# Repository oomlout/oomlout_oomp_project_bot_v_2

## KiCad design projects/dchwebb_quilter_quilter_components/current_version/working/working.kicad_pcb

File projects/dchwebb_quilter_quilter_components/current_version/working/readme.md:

# quilter
 
## summary 
* id: dchwebb_quilter_quilter_components
* user: dchwebb
* name: quilter
* board: quilter_components
* repo: https://github.com/dchwebb/Quilter
* src_file_repo_kicad_pcb: Quilter_Components.kicad_pcb
* src_file_repo_kicad_pcb_link: https://github.com/dchwebb/Quilter/tree/main/Quilter_Components.kicad_pcb
* src_file_repo_kicad_sch: Filter_Voice.kicad_sch
* src_file_repo_kicad_sch_link: https://github.com/dchwebb/Quilter/tree/main/Filter_Voice.kicad_sch

* src_file_repo_sch: 
* src_file_repo_sch_link: https://github.com/dchwebb/Quilter/tree/main/
* full details link: https://github.com/oomlout/oomlout_oomp_project_bot_v_2/tree/main/projects/dchwebb_quilter_quilter_components/current_version/working

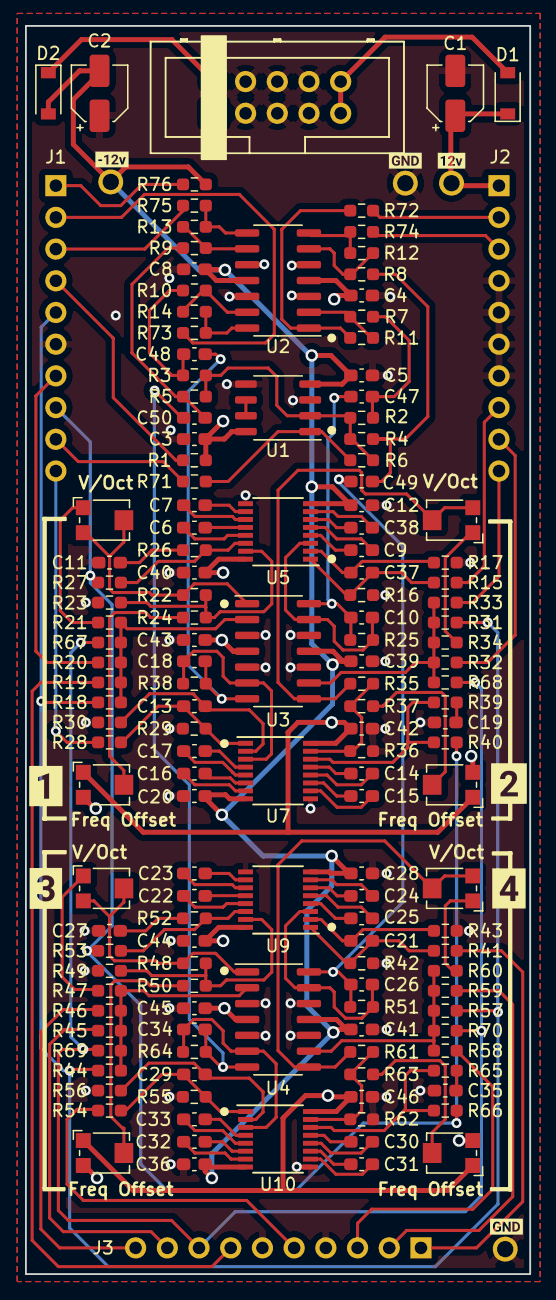
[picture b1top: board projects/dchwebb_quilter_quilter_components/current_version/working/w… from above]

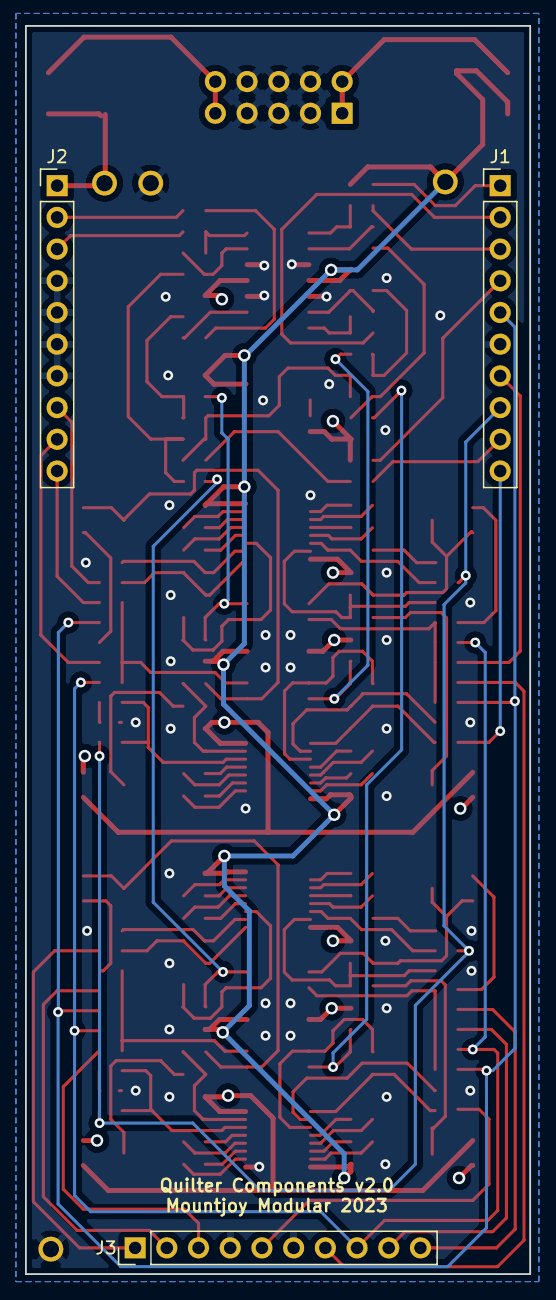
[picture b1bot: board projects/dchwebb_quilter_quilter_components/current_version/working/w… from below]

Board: 4 copper layers, 40.4 x 100.0 mm, 160 parts (3 on the bottom side), 118 nets.

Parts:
C1, C2: 22uF; CP_Elec_4x5.8
C3, C4, C5, C8, C12, C20, C28, C36, C39, C40, C41, C42, C43, C44, C45, C46: 1uF; C_0603_1608Metric_Pad1.08x0.95mm_HandSolder
C6, C7, C14, C15, C16, C22, C23, C24, C30, C31, C32, C38: 6.8nF_C0G; C_0603_1608Metric_Pad1.08x0.95mm_HandSolder
C9, C17, C25, C33: 560pF_C0G; C_0603_1608Metric_Pad1.08x0.95mm_HandSolder
C10, C18, C26, C34: 100pF; C_0603_1608Metric_Pad1.08x0.95mm_HandSolder
C11, C19, C27, C35: 10nF; C_0603_1608Metric_Pad1.08x0.95mm_HandSolder
C13, C21, C29, C37: 3.3nF; C_0603_1608Metric_Pad1.08x0.95mm_HandSolder
C47, C48, C49, C50: 10uF; C_0603_1608Metric_Pad1.08x0.95mm_HandSolder
D1, D2: 1N5819; D_SOD-123
FREQ_OFFSET1, FREQ_OFFSET2, FREQ_OFFSET3, FREQ_OFFSET4: 50k; Potentiometer_Bourns_TC33X_Vertical
J1, J2, J3: Conn_01x10_Male; PinHeader_1x10_P2.54mm_Vertical
J4: Eurorack_10_pin_power; Eurorack_10_pin_header
R1, R76: 14k; R_0603_1608Metric_Pad0.98x0.95mm_HandSolder
R2, R3, R4, R5, R7, R8, R9, R10, R11, R12, R13, R14: 10k; R_0603_1608Metric_Pad0.98x0.95mm_HandSolder
R6: 4.7k; R_0603_1608Metric_Pad0.98x0.95mm_HandSolder
R15, R28, R41, R54: 68k; R_0603_1608Metric_Pad0.98x0.95mm_HandSolder
R16, R17, R29, R30, R42, R43, R55, R56: 200; R_0603_1608Metric_Pad0.98x0.95mm_HandSolder
R18, R20, R22, R31, R33, R35, R44, R46, R48, R57, R59, R61, R67, R68, R69, R70: 100k; R_0603_1608Metric_Pad0.98x0.95mm_HandSolder
R19, R32, R45, R58: 220k; R_0603_1608Metric_Pad0.98x0.95mm_HandSolder
R21, R34, R47, R60: 160k; R_0603_1608Metric_Pad0.98x0.95mm_HandSolder
R23, R36, R49, R62, R71, R72, R73, R74, R75: 1k; R_0603_1608Metric_Pad0.98x0.95mm_HandSolder
R24, R37, R50, R63: 499k; R_0603_1608Metric_Pad0.98x0.95mm_HandSolder
R25, R38, R51, R64: 33k; R_0603_1608Metric_Pad0.98x0.95mm_HandSolder
R26, R39, R52, R65: 499; R_0603_1608Metric_Pad0.98x0.95mm_HandSolder
R27, R40, R53, R66: 24k; R_0603_1608Metric_Pad0.98x0.95mm_HandSolder
TP1, TP2, TP3, TP4: TestPoint; 1.3mm_Test_Point
U1: TL072; SO-8_3.9x4.9mm_P1.27mm
U2, U3, U4: TL074; SOIC-14_3.9x8.7mm_P1.27mm
U5, U7, U9, U10: SSI2144; SSOP-16_3.9x4.9mm_P0.635mm
V_OCT1, V_OCT2, V_OCT3, V_OCT4: 50k; Potentiometer_Bourns_TC33X_Vertical
kibuzzard-63F9EC4B: G***; kibuzzard-63F9EC4B
kibuzzard-63F9ECEE: G***; kibuzzard-63F9ECEE
kibuzzard-63FCE890: G***; kibuzzard-63FCE890
kibuzzard-63FCEF0D: G***; kibuzzard-63FCEF0D
kibuzzard-640237A8: G***; kibuzzard-640237A8
kibuzzard-640237DF, kibuzzard-640237DF#2: G***; kibuzzard-640237DF
kibuzzard-640237FD: G***; kibuzzard-640237FD

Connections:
+12V: C1.1, C3.1, C4.1, C40.1, C42.1, C43.1, C44.1, C45.1, C46.1, D1.1 (K), FREQ_OFFSET1.1, FREQ_OFFSET2.1, FREQ_OFFSET3.1, FREQ_OFFSET4.1, J2.1, R1.1, TP1.1, U1.8 (V+), U2.4 (V+), U3.4 (V+), U4.4 (V+), U5.16 (V+), U7.16 (V+), U9.16 (V+), U10.16 (V+)
-12V: C2.2, C5.1, C8.1, C12.2, C20.2, C28.2, C36.2, C39.1, C41.1, D2.2 (A), FREQ_OFFSET1.3, FREQ_OFFSET2.3, FREQ_OFFSET3.3, FREQ_OFFSET4.3, R76.1, TP2.1, U1.4 (V-), U2.11 (V-), U3.11 (V-), U4.11 (V-), U5.8 (V-), U7.8 (V-), U9.8 (V-), U10.8 (V-)
/+12V_IN: D1.2 (A), J4.9, J4.10
/-12V_IN: D2.1 (K), J4.1, J4.2
/AUDIO_BUFF1: J2.2, R72.2
/AUDIO_BUFF2: J1.2, R73.2
/AUDIO_BUFF3: J2.3, R74.2
/AUDIO_BUFF4: J1.3, R75.2
/AUDIO_IN1: J2.8, R15.2
/AUDIO_IN2: J1.10, R28.2
/AUDIO_IN3: J3.1, R41.2
/AUDIO_IN4: J3.5, R54.2
/AUDIO_MIX: J1.9, R71.2
/Audio_Out1: C47.1, R2.2, R7.2
/Audio_Out2: C48.1, R3.2, R10.2
/Audio_Out3: C49.1, R4.2, R8.2
/Audio_Out4: C50.1, R5.2, R9.2
/FREQ_CV_DAMP1: J3.7, R19.2
/FREQ_CV_DAMP2: J2.9, R32.2
/FREQ_CV_DAMP3: J3.9, R45.2
/FREQ_CV_DAMP4: J3.3, R58.2
/FREQ_JACK: J3.8, R67.2, R68.2, R69.2, R70.2
/FREQ_POT: J1.5, R18.2, R31.2, R44.2, R57.2
/FREQ_POT_5V: J1.4, R1.2
/FREQ_POT_-5V: J1.1, R76.2
/FREQ_V_OCT1: J1.7, R20.2
/FREQ_V_OCT2: J2.10, R33.2
/FREQ_V_OCT3: J3.10, R46.2
/FREQ_V_OCT4: J3.2, R59.2
/Filter_Voice1/FREQ_CTRL: R22.1, R23.1, R24.1, U5.15 (FREQ_CTRL)
/Filter_Voice1/Q_CTRL: R26.2, R27.2, U5.14 (Q_CTRL)
/Filter_Voice2/FREQ_CTRL: R35.1, R36.1, R37.1, U7.15 (FREQ_CTRL)
/Filter_Voice2/Q_CTRL: R39.2, R40.2, U7.14 (Q_CTRL)
/Filter_Voice3/FREQ_CTRL: R48.1, R49.1, R50.1, U9.15 (FREQ_CTRL)
/Filter_Voice3/Q_CTRL: R52.2, R53.2, U9.14 (Q_CTRL)
/Filter_Voice4/FREQ_CTRL: R61.1, R62.1, R63.1, U10.15 (FREQ_CTRL)
/Filter_Voice4/Q_CTRL: R65.2, R66.2, U10.14 (Q_CTRL)
/Q_POT: J1.8, R27.1, R40.1, R53.1, R66.1
GND: C1.2, C2.1, C3.2, C4.2, C5.2, C8.2, C11.2, C12.1, C19.2, C20.1, C27.2, C28.1, C35.2, C36.1, C39.2, C40.2, C41.2, C42.2, C43.2, C44.2, C45.2, C46.2, J1.6, J2.4, J2.5, J2.6, J2.7, J3.4, J3.6, J4.3, J4.4, J4.5, J4.6, J4.7, J4.8, R16.1, R17.2, R23.2, R29.1, R30.2, R36.2, R42.1, R43.2, R49.2, R55.1, R56.2, R62.2, TP3.1, TP4.1, U1.3 (+), U1.5 (+), U2.3 (+), U2.5 (+), U2.10 (+), U2.12 (+), U3.3 (+), U3.5 (+), U3.10 (+), U3.12 (+), U4.3 (+), U4.5 (+), U4.10 (+), U4.12 (+), U5.9 (GND), U7.9 (GND), U9.9 (GND), U10.9 (GND)
unnamed: C6.1, U5.13 (C1A)
unnamed: C6.2, U5.12 (C1B)
unnamed: C7.1, U5.11 (C2A)
unnamed: C7.2, U5.10 (C2B)
unnamed: C9.1, U5.4 (C4A)
unnamed: C9.2, U5.5 (C4B)
unnamed: C10.1, C47.2, R25.1, U3.14
unnamed: C10.2, R25.2, U3.13 (-), U5.3 (OUT)
unnamed: C11.1, R26.1
unnamed: C13.1, R30.1, U7.2 (SIG_IN-)
unnamed: C13.2, R28.1, R29.2, U7.1 (SIG_IN+)
unnamed: C14.1, U7.13 (C1A)
unnamed: C14.2, U7.12 (C1B)
unnamed: C15.1, U7.11 (C2A)
unnamed: C15.2, U7.10 (C2B)
unnamed: C16.1, U7.6 (C3A)
unnamed: C16.2, U7.7 (C3B)
unnamed: C17.1, U7.4 (C4A)
unnamed: C17.2, U7.5 (C4B)
unnamed: C18.1, C48.2, R38.1, U3.7
unnamed: C18.2, R38.2, U3.6 (-), U7.3 (OUT)
unnamed: C19.1, R39.1
unnamed: C21.1, R43.1, U9.2 (SIG_IN-)
unnamed: C21.2, R41.1, R42.2, U9.1 (SIG_IN+)
unnamed: C22.1, U9.13 (C1A)
unnamed: C22.2, U9.12 (C1B)
unnamed: C23.1, U9.11 (C2A)
unnamed: C23.2, U9.10 (C2B)
unnamed: C24.1, U9.6 (C3A)
unnamed: C24.2, U9.7 (C3B)
unnamed: C25.1, U9.4 (C4A)
unnamed: C25.2, U9.5 (C4B)
unnamed: C26.1, C49.2, R51.1, U4.14
unnamed: C26.2, R51.2, U4.13 (-), U9.3 (OUT)
unnamed: C27.1, R52.1
unnamed: C29.1, R56.1, U10.2 (SIG_IN-)
unnamed: C29.2, R54.1, R55.2, U10.1 (SIG_IN+)
unnamed: C30.1, U10.13 (C1A)
unnamed: C30.2, U10.12 (C1B)
unnamed: C31.1, U10.11 (C2A)
unnamed: C31.2, U10.10 (C2B)
unnamed: C32.1, U10.6 (C3A)
unnamed: C32.2, U10.7 (C3B)
unnamed: C33.1, U10.4 (C4A)
unnamed: C33.2, U10.5 (C4B)
unnamed: C34.1, C50.2, R64.1, U4.7
unnamed: C34.2, R64.2, U4.6 (-), U10.3 (OUT)
unnamed: C35.1, R65.1
unnamed: C37.1, R17.1, U5.2 (SIG_IN-)
unnamed: C37.2, R15.1, R16.2, U5.1 (SIG_IN+)
unnamed: C38.1, U5.6 (C3A)
unnamed: C38.2, U5.7 (C3B)
unnamed: FREQ_OFFSET1.2, R24.2
unnamed: FREQ_OFFSET2.2, R37.2
unnamed: FREQ_OFFSET3.2, R50.2
unnamed: FREQ_OFFSET4.2, R63.2
unnamed: R2.1, R3.1, R4.1, R5.1, R6.2, U1.2 (-)
unnamed: R6.1, R71.1, U1.1
unnamed: R10.1, R14.2, U2.13 (-)
unnamed: R11.1, R72.1, U2.1
unnamed: R7.1, R11.2, U2.2 (-)
unnamed: R12.1, R74.1, U2.7
unnamed: R8.1, R12.2, U2.6 (-)
unnamed: R13.1, R75.1, U2.8
unnamed: R9.1, R13.2, U2.9 (-)
unnamed: R14.1, R73.1, U2.14
unnamed: R18.1, R19.1, R20.1, R21.2, R67.1, U3.2 (-)
unnamed: R21.1, V_OCT1.1
unnamed: R22.2, U3.1, V_OCT1.2, V_OCT1.3
unnamed: R31.1, R32.1, R33.1, R34.2, R68.1, U3.9 (-)
unnamed: R34.1, V_OCT2.1
unnamed: R35.2, U3.8, V_OCT2.2, V_OCT2.3
unnamed: R44.1, R45.1, R46.1, R47.2, R69.1, U4.2 (-)
unnamed: R47.1, V_OCT3.1
unnamed: R48.2, U4.1, V_OCT3.2, V_OCT3.3
unnamed: R57.1, R58.1, R59.1, R60.2, R70.1, U4.9 (-)
unnamed: R60.1, V_OCT4.1
unnamed: R61.2, U4.8, V_OCT4.2, V_OCT4.3
unnamed: U1.6 (-), U1.7

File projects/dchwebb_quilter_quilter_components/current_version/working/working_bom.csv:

"Id";"Designator";"Footprint";"Quantity";"Designation";"Supplier and ref";
1;"R44,R35,R57,R33,R46,R22,R18,R69,R68,R67,R20,R70,R48,R59,R31,R61";"R_0603_1608Metric_Pad0.98x0.95mm_HandSolder";16;"100k";;;
2;"R23,R75,R73,R74,R62,R36,R72,R71,R49";"R_0603_1608Metric_Pad0.98x0.95mm_HandSolder";9;"1k";;;
3;"C4,C45,C3,C28,C40,C5,C46,C36,C12,C44,C8,C41,C43,C42,C39,C20";"C_0603_1608Metric_Pad1.08x0.95mm_HandSolder";16;"1uF";;;
4;"D1,D2";"D_SOD-123";2;"1N5819";;;
5;"R53,R27,R40,R66";"R_0603_1608Metric_Pad0.98x0.95mm_HandSolder";4;"24k";;;
6;"C38,C14,C30,C15,C31,C22,C24,C16,C6,C23,C32,C7";"C_0603_1608Metric_Pad1.08x0.95mm_HandSolder";12;"6.8nF_C0G";;;
7;"R58,R19,R32,R45";"R_0603_1608Metric_Pad0.98x0.95mm_HandSolder";4;"220k";;;
8;"C10,C18,C34,C26";"C_0603_1608Metric_Pad1.08x0.95mm_HandSolder";4;"100pF";;;
9;"R2,R9,R13,R10,R3,R7,R12,R8,R4,R14,R5,R11";"R_0603_1608Metric_Pad0.98x0.95mm_HandSolder";12;"10k";;;
10;"R21,R34,R47,R60";"R_0603_1608Metric_Pad0.98x0.95mm_HandSolder";4;"160k";;;
11;"R42,R16,R56,R55,R30,R17,R43,R29";"R_0603_1608Metric_Pad0.98x0.95mm_HandSolder";8;"200";;;
12;"C11,C19,C27,C35";"C_0603_1608Metric_Pad1.08x0.95mm_HandSolder";4;"10nF";;;
13;"R51,R38,R64,R25";"R_0603_1608Metric_Pad0.98x0.95mm_HandSolder";4;"33k";;;
14;"C21,C37,C13,C29";"C_0603_1608Metric_Pad1.08x0.95mm_HandSolder";4;"3.3nF";;;
15;"R6";"R_0603_1608Metric_Pad0.98x0.95mm_HandSolder";1;"4.7k";;;
16;"R54,R28,R41,R15";"R_0603_1608Metric_Pad0.98x0.95mm_HandSolder";4;"68k";;;
17;"C49,C47,C50,C48";"C_0603_1608Metric_Pad1.08x0.95mm_HandSolder";4;"10uF";;;
18;"U1";"SO-8_3.9x4.9mm_P1.27mm";1;"TL072";;;

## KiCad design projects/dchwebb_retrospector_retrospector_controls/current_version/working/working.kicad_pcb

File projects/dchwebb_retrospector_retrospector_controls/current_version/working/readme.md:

# retrospector
 
## summary 
* id: dchwebb_retrospector_retrospector_controls
* user: dchwebb
* name: retrospector
* board: retrospector_controls
* repo: https://github.com/dchwebb/Retrospector
* src_file_repo_kicad_pcb: Hardware/Retrospector_Components.kicad_pcb
* src_file_repo_kicad_pcb_link: https://github.com/dchwebb/Retrospector/tree/master/Hardware/Retrospector_Components.kicad_pcb
* src_file_repo_kicad_sch: Hardware/Retrospector_Components.kicad_sch
* src_file_repo_kicad_sch_link: https://github.com/dchwebb/Retrospector/tree/master/Hardware/Retrospector_Components.kicad_sch

* src_file_repo_sch: Hardware/Retrospector_Components.sch
* src_file_repo_sch_link: https://github.com/dchwebb/Retrospector/tree/master/Hardware/Retrospector_Components.sch
* full details link: https://github.com/oomlout/oomlout_oomp_project_bot_v_2/tree/main/projects/dchwebb_retrospector_retrospector_controls/current_version/working

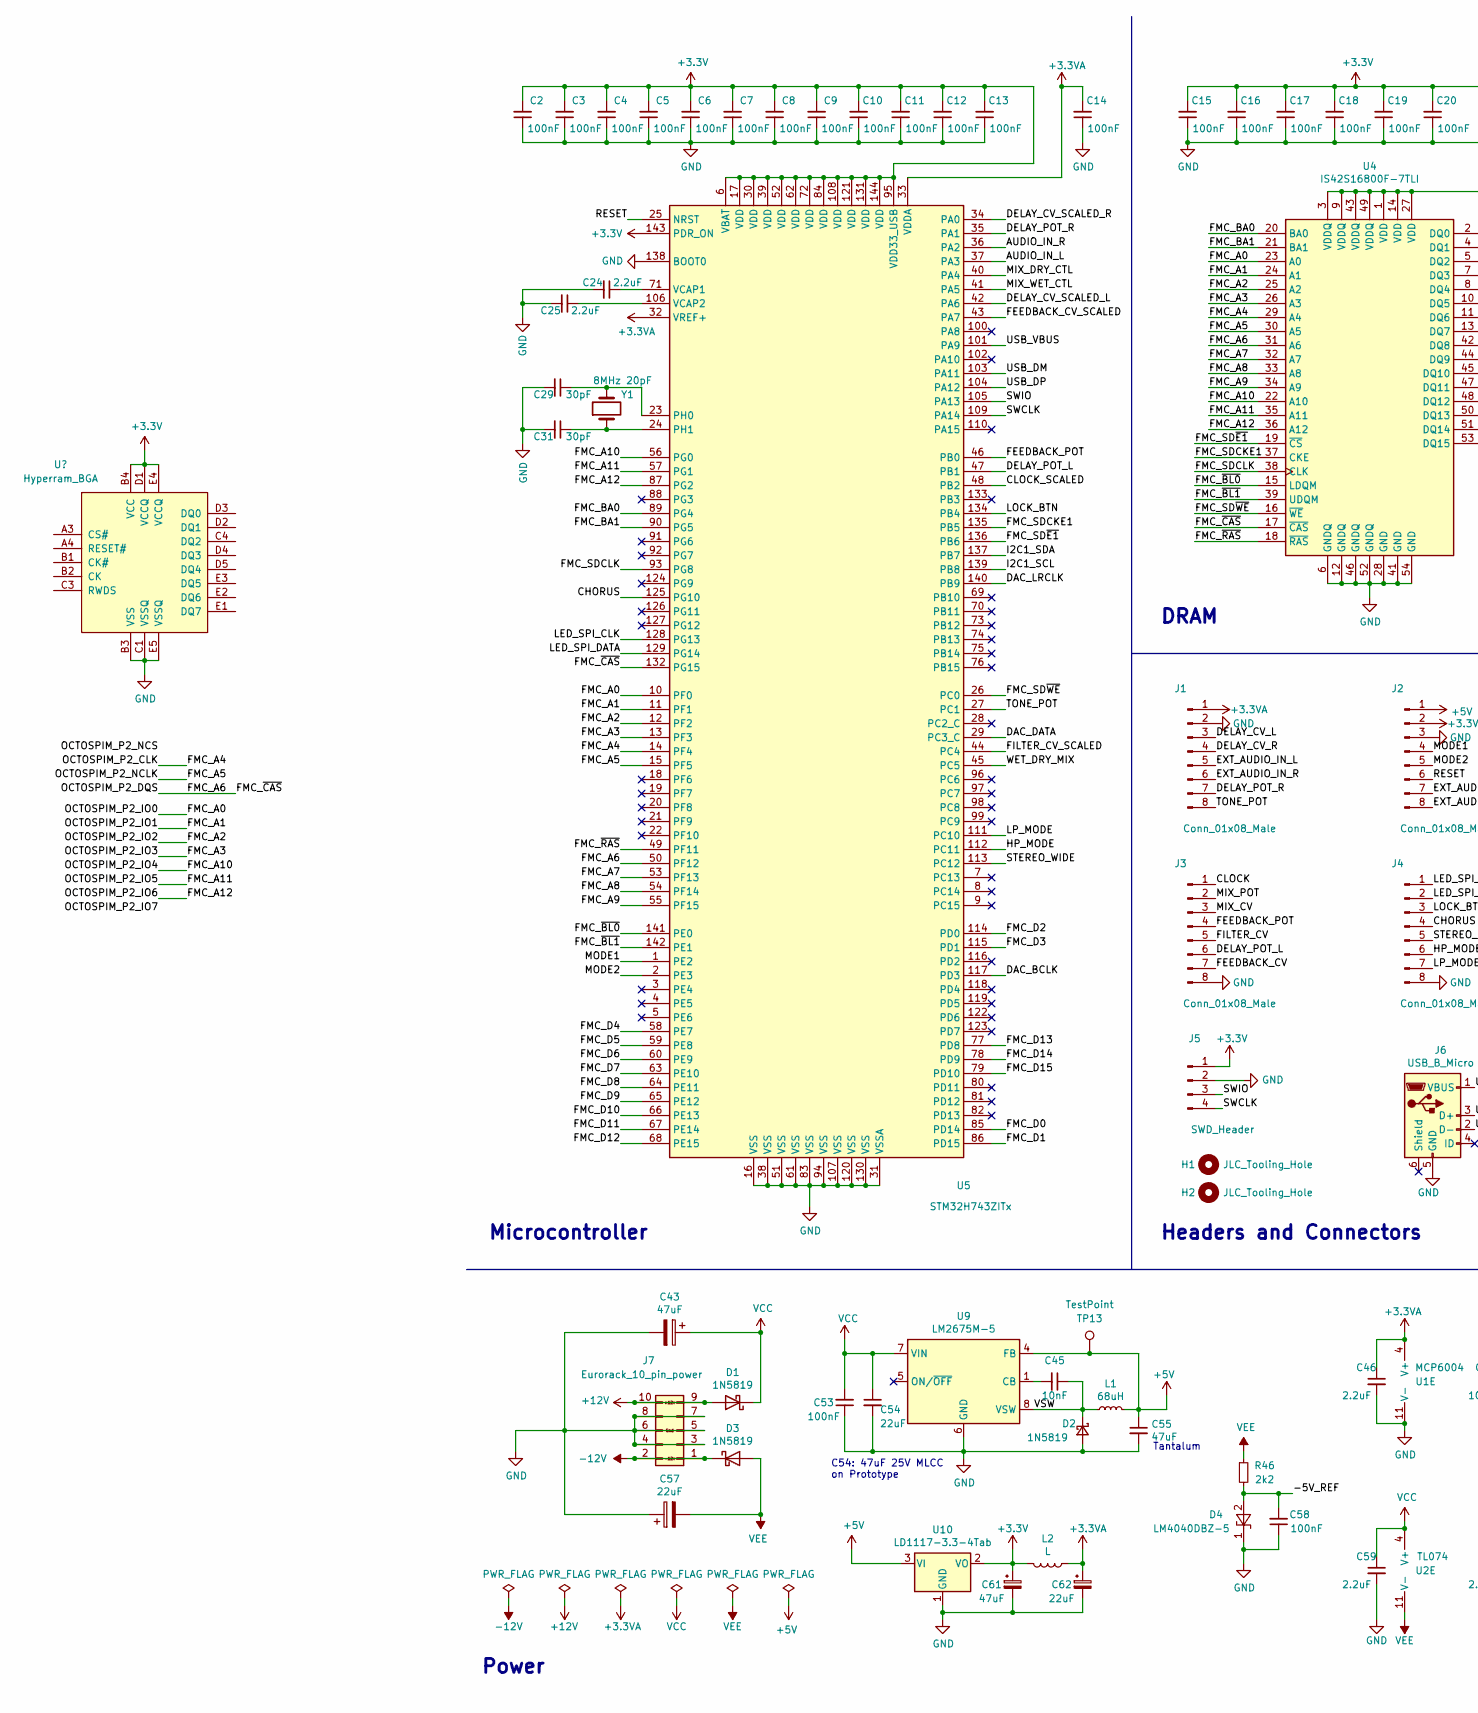
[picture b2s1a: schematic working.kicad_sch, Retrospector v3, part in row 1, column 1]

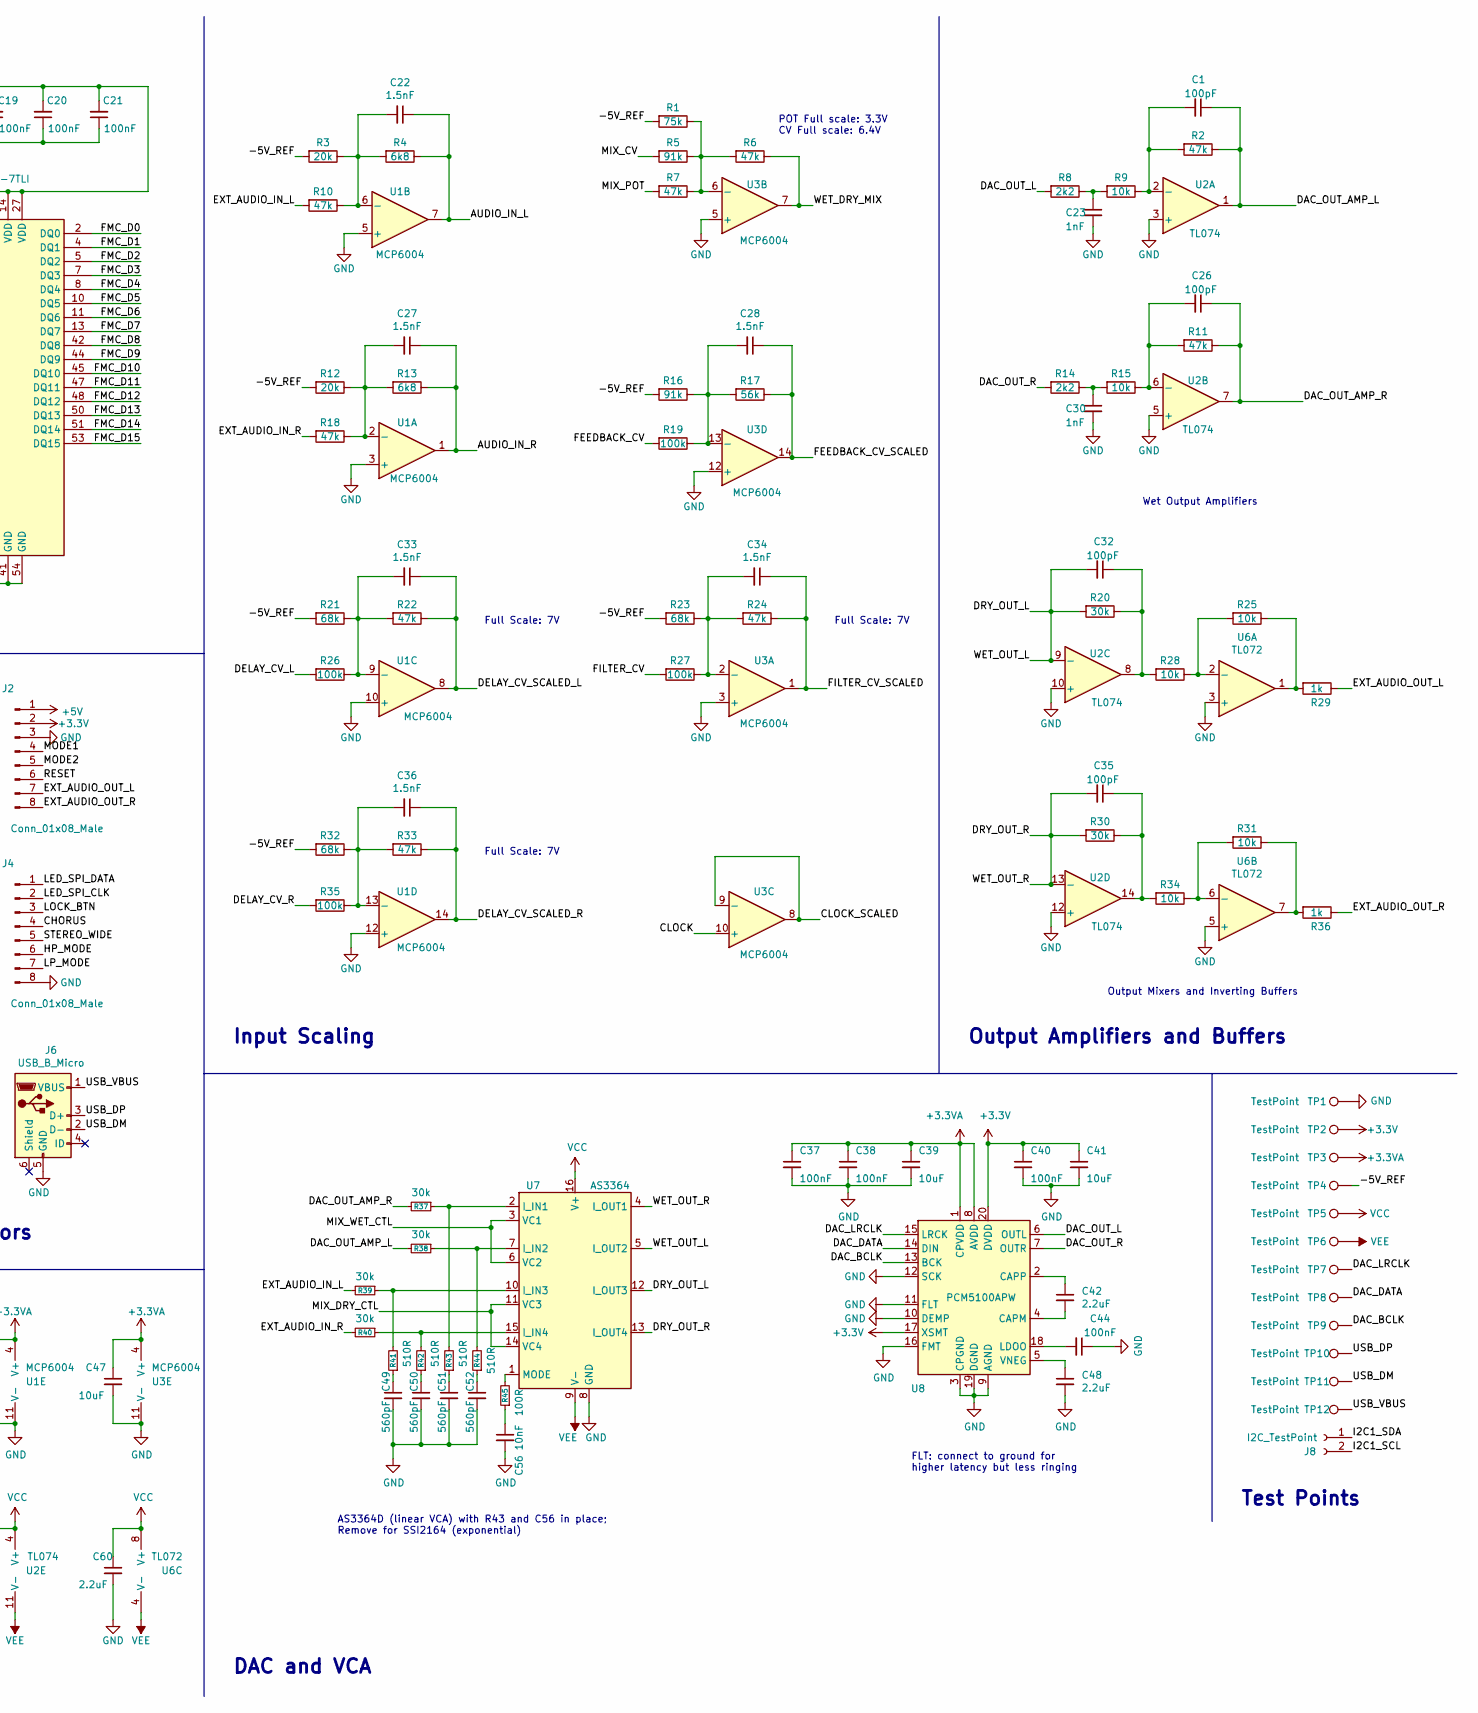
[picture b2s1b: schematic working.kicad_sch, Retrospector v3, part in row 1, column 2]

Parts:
C1, C26, C32, C35: 100pF; C_0603_HandSoldering; Part_Number C14858
C2, C3, C4, C5, C6, C7, C8, C9, C10, C11, C12, C13, C14, C15, C16, C17, C18, C19, C20, C21, C37, C38, C40, C44, C58: 100nF; C_0603_HandSoldering; Part_Number C14663
C22, C27, C28, C33, C34, C36: 1.5nF; C_0603_HandSoldering; Part_Number C1595
C23, C30: 1nF; C_0603_HandSoldering; Part_Number C1588
C24, C25, C42, C46, C48, C59, C60: 2.2uF; C_0603_HandSoldering; Part_Number C23630
C29, C31: 30pF; C_0603_HandSoldering; Part_Number C22397
C39, C41, C47: 10uF; C_0805; Part_Number C15850
C43, C61: 47uF; CP_Elec_5x5.8; Part_Number C134798
C45, C56: 10nF; C_0603_HandSoldering; Part_Number C57112
C49, C50, C51, C52: 560pF; C_0603_HandSoldering; Part_Number C84721
C53: 100nF; C_0603_HandSoldering
C54: 22uF; C_1210
C55: 47uF; C_1210
C57, C62: 22uF; CP_Elec_4x5.8; Part_Number C134793
D1, D2, D3: 1N5819; D_SOD-123; Part_Number C8598
D4: LM4040DBZ-5; SOT-23; Part_Number C156291
H1, H2: JLC_Tooling_Hole; JLC_SMT_Tooling_Hole
J1, J2, J3, J4: Conn_01x08_Male; Pin_Header_Straight_1x08_Pitch2.54mm
J5: SWD_Header; SWD_header
J6: USB_B_Micro; USB_Micro-B_Amphenol
J7: Eurorack_10_pin_power; Eurorack_10_pin_header
J8: I2C_TestPoint; Pin_Header_Straight_1x02_Pitch2.54mm
L1: 68uH; TDK_Inductor_6.9x7.2
L2: L; L_0805_HandSoldering; Part_Number C1046
R1: 75k; R_0603_HandSoldering; Part_Number C23242
R2, R6, R7, R10, R11, R18, R22, R24, R33: 47k; R_0603_HandSoldering; Part_Number C25819
R3, R12: 20k; R_0603_HandSoldering; Part_Number C4184
R4, R13: 6k8; R_0603_HandSoldering; Part_Number C23212
R5, R16: 91k; R_0603_HandSoldering; Part_Number C23265
R8, R14, R46: 2k2; R_0603_HandSoldering; Part_Number C4190
R9, R15, R25, R28, R31, R34: 10k; R_0603_HandSoldering; Part_Number C25804
R17: 56k; R_0603_HandSoldering; Part_Number C23206
R19, R26, R27, R35: 100k; R_0603_HandSoldering; Part_Number C25803
R20, R30, R37, R38, R39, R40: 30k; R_0603_HandSoldering; Part_Number C22984
R21, R23, R32: 68k; R_0603_HandSoldering; Part_Number C23231
R29, R36: 1k; R_0603_HandSoldering; Part_Number C21190
R41, R42, R43, R44: 510R; R_0603_HandSoldering; Part_Number C23193
R45: 100R; R_0603_HandSoldering; Part_Number C22775
TP1, TP2, TP3, TP4, TP5, TP6: TestPoint; 1.3mm_Test_Point
TP7, TP8, TP9, TP10, TP11, TP12, TP13: TestPoint; Measurement_Point_Square-SMD-Pad_Small
U1, U3: MCP6004; SOIC-14_N; Part_Number C116668
U2: TL074; SOIC-14_N; Part_Number C6964
U4: IS42S16800F-7TLI; TSOP-II-54_22.2x10.16mm_P0.8mm; Part_Number C91278
U5: STM32H743ZITx; LQFP-144_20x20mm_P0.5mm; Part_Number C114408
U6: TL072; SOIC-8_3.9x4.9mm_Pitch1.27mm; Part_Number C6961
U7: AS3364; SOIC-16_3.9x9.9mm_Pitch1.27mm
U8: PCM5100APW; SSOP-20_4.4x6.5mm_Pitch0.65mm_Round_Pads; Part_Number C131154
U9: LM2675M-5; SOIC-8_3.9x4.9mm_Pitch1.27mm; Part_Number C180371
U10: LD1117-3.3-4Tab; SOT-223-3_TabPin2
Y1: 8MHz 20pF; Crystal_SMD_5032-2pin_5.0x3.2mm_HandSoldering; Part_Number C115962

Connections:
+3.3VA: C14.2, C37.1, C38.1, C39.1, C46.1, C47.1, C62.1, J1.1, L2.1, TP3.1, U1.4 (V+), U3.4 (V+), U5.32 (VREF+), U5.33 (VDDA), U8.1 (CPVDD), U8.8 (AVDD)
+3V3: C2.2, C3.2, C4.2, C5.2, C6.2, C7.2, C8.2, C9.2, C10.2, C11.2, C12.2, C13.2, C15.2, C16.2, C17.2, C18.2, C19.2, C20.2, C21.2, C40.1, C41.1, C61.1, J2.2, J5.1, L2.2, TP2.1, U4.1 (VDD), U4.3 (VDDQ), U4.9 (VDDQ), U4.14 (VDD), U4.27 (VDD), U4.43 (VDDQ), U4.49 (VDDQ), U5.6 (VBAT), U5.17 (VDD), U5.30 (VDD), U5.39 (VDD), U5.52 (VDD), U5.62 (VDD), U5.72 (VDD), U5.84 (VDD), U5.95 (VDD33_USB), U5.108 (VDD), U5.121 (VDD), U5.131 (VDD), U5.143 (PDR_ON), U5.144 (VDD), U8.17 (XSMT), U8.20 (DVDD), U10.2 (VO)
+5V: C55.1, J2.1, L1.2, TP13.1, U9.4 (FB), U10.3 (VI)
+12V: D1.2 (A), J7.9, J7.10
-12V: D3.1 (K), J7.1, J7.2
/-5V_REF: C58.2, D4.2 (A), R1.2, R3.2, R12.2, R16.2, R21.2, R23.2, R32.2, R46.2, TP4.1
/AUDIO_IN_L: C22.1, R4.1, U1.7, U5.37 (PA3)
/AUDIO_IN_R: C27.1, R13.1, U1.1, U5.36 (PA2)
/CHORUS: J4.4, U5.125 (PG10)
/CLOCK: J3.1, U3.10 (+)
/CLOCK_SCALED: U3.8, U3.9 (-), U5.48 (PB2)
/DAC_BCLK: TP9.1, U5.117 (PD3), U8.13 (BCK)
/DAC_DATA: TP8.1, U5.29 (PC3_C), U8.14 (DIN)
/DAC_LRCLK: TP7.1, U5.140 (PB9), U8.15 (LRCK)
/DAC_OUT_AMP_L: C1.1, R2.1, R38.2, U2.1
/DAC_OUT_AMP_R: C26.1, R11.1, R37.2, U2.7
/DAC_OUT_L: R8.2, U8.6 (OUTL)
/DAC_OUT_R: R14.2, U8.7 (OUTR)
/DELAY_CV_L: J1.3, R26.2
/DELAY_CV_R: J1.4, R35.2
/DELAY_CV_SCALED_L: C33.1, R22.1, U1.8, U5.42 (PA6)
/DELAY_CV_SCALED_R: C36.1, R33.1, U1.14, U5.34 (PA0)
/DELAY_POT_L: J3.6, U5.47 (PB1)
/DELAY_POT_R: J1.7, U5.35 (PA1)
/DRY_OUT_L: C32.2, R20.2, U2.9 (-), U7.5 (I_OUT2), U7.12 (I_OUT3)
/DRY_OUT_R: C35.2, R30.2, U2.13 (-), U7.4 (I_OUT1), U7.13 (I_OUT4)
/EXT_AUDIO_IN_L: J1.5, R10.2, R39.2
/EXT_AUDIO_IN_R: J1.6, R18.2, R40.2
/EXT_AUDIO_OUT_L: J2.7, R29.1
/EXT_AUDIO_OUT_R: J2.8, R36.1
/FEEDBACK_CV: J3.7, R19.2
/FEEDBACK_CV_SCALED: C28.1, R17.1, U3.14, U5.43 (PA7)
/FEEDBACK_POT: J3.4, U5.46 (PB0)
/FILTER_CV: J3.5, R27.2
/FILTER_CV_SCALED: C34.1, R24.1, U3.1, U5.44 (PC4)
/FMC_A0: U4.23 (A0), U5.10 (PF0)
/FMC_A1: U4.24 (A1), U5.11 (PF1)
/FMC_A2: U4.25 (A2), U5.12 (PF2)
/FMC_A3: U4.26 (A3), U5.13 (PF3)
/FMC_A4: U4.29 (A4), U5.14 (PF4)
/FMC_A5: U4.30 (A5), U5.15 (PF5)
/FMC_A7: U4.32 (A7), U5.53 (PF13)
/FMC_A8: U4.33 (A8), U5.54 (PF14)
/FMC_A9: U4.34 (A9), U5.55 (PF15)
/FMC_A10: U4.22 (A10), U5.56 (PG0)
/FMC_A11: U4.35 (A11), U5.57 (PG1)
/FMC_A12: U4.36 (A12), U5.87 (PG2)
/FMC_BA0: U4.20 (BA0), U5.89 (PG4)
/FMC_BA1: U4.21 (BA1), U5.90 (PG5)
/FMC_D0: U4.2 (DQ0), U5.85 (PD14)
/FMC_D1: U4.4 (DQ1), U5.86 (PD15)
/FMC_D2: U4.5 (DQ2), U5.114 (PD0)
/FMC_D3: U4.7 (DQ3), U5.115 (PD1)
/FMC_D4: U4.8 (DQ4), U5.58 (PE7)
/FMC_D5: U4.10 (DQ5), U5.59 (PE8)
/FMC_D6: U4.11 (DQ6), U5.60 (PE9)
/FMC_D7: U4.13 (DQ7), U5.63 (PE10)
/FMC_D8: U4.42 (DQ8), U5.64 (PE11)
/FMC_D9: U4.44 (DQ9), U5.65 (PE12)
/FMC_D10: U4.45 (DQ10), U5.66 (PE13)
/FMC_D11: U4.47 (DQ11), U5.67 (PE14)
/FMC_D12: U4.48 (DQ12), U5.68 (PE15)
/FMC_D13: U4.50 (DQ13), U5.77 (PD8)
/FMC_D14: U4.51 (DQ14), U5.78 (PD9)
/FMC_D15: U4.53 (DQ15), U5.79 (PD10)
/FMC_SDCKE1: U4.37 (CKE), U5.135 (PB5)
/FMC_SDCLK: U4.38 (CLK), U5.93 (PG8)
/FMC_SD~E1: U4.19 (~CS), U5.136 (PB6)
/FMC_SD~WE: U4.16 (~WE), U5.26 (PC0)
/FMC_~BL0: U4.15 (LDQM), U5.141 (PE0)
/FMC_~BL1: U4.39 (UDQM), U5.142 (PE1)
/FMC_~RAS: U4.18 (~RAS), U5.49 (PF11)
/HP_MODE: J4.6, U5.112 (PC11)
/I2C1_SCL: J8.2, U5.139 (PB8)
/I2C1_SDA: J8.1, U5.137 (PB7)
/LED_SPI_CLK: J4.2, U5.128 (PG13)
/LED_SPI_DATA: J4.1, U5.129 (PG14)
/LOCK_BTN: J4.3, U5.134 (PB4)
/LP_MODE: J4.7, U5.111 (PC10)
/MIX_CV: J3.3, R5.2
/MIX_DRY_CTL: U5.40 (PA4), U7.11 (VC3), U7.14 (VC4)
/MIX_POT: J3.2, R7.2
/MIX_WET_CTL: U5.41 (PA5), U7.3 (VC1), U7.6 (VC2)
/MODE1: J2.4, U5.1 (PE2)
/MODE2: J2.5, U5.2 (PE3)
/RESET: J2.6, U5.25 (NRST)
/STEREO_WIDE: J4.5, U5.113 (PC12)
/SWCLK: J5.4, U5.109 (PA14)
/SWIO: J5.3, U5.105 (PA13)
/TONE_POT: J1.8, U5.27 (PC1)
/USB_DM: J6.2 (D-), TP11.1, U5.103 (PA11)
/USB_DP: J6.3 (D+), TP10.1, U5.104 (PA12)
/USB_VBUS: J6.1 (VBUS), TP12.1, U5.101 (PA9)
/VSW: C45.1, D2.1 (K), L1.1, U9.8 (VSW)
/WET_DRY_MIX: R6.1, U3.7, U5.45 (PC5)
GND: C2.1, C3.1, C4.1, C5.1, C6.1, C7.1, C8.1, C9.1, C10.1, C11.1, C12.1, C13.1, C14.1, C15.1, C16.1, C17.1, C18.1, C19.1, C20.1, C21.1, C23.2, C24.2, C25.2, C29.2, C30.2, C31.2, C37.2, C38.2, C39.2, C40.2, C41.2, C43.2, C44.1, C46.2, C47.2, C48.2, C49.2, C50.2, C51.2, C52.2, C53.1, C54.2, C55.2, C56.2, C57.1, C58.1, C59.2, C60.2, C61.2, C62.2, D2.2 (A), D4.1 (K), J1.2, J2.3, J3.8, J4.8, J5.2, J6.5 (GND), J7.3, J7.4, J7.5, J7.6, J7.7, J7.8, TP1.1, U1.3 (+), U1.5 (+), U1.10 (+), U1.11 (V-), U1.12 (+), U2.3 (+), U2.5 (+), U2.10 (+), U2.12 (+), U3.3 (+), U3.5 (+), U3.11 (V-), U3.12 (+), U4.6 (GNDQ), U4.12 (GNDQ), U4.28 (GND), U4.41 (GND), U4.46 (GNDQ), U4.52 (GNDQ), U4.54 (GND), U5.16 (VSS), U5.31 (VSSA), U5.38 (VSS), U5.51 (VSS), U5.61 (VSS), U5.83 (VSS), U5.94 (VSS), U5.107 (VSS), U5.120 (VSS), U5.130 (VSS), U5.138 (BOOT0), U6.3 (+), U6.5 (+), U7.8 (GND), U8.3 (CPGND), U8.9 (AGND), U8.10 (DEMP), U8.11 (FLT), U8.12 (SCK), U8.16 (FMT), U8.19 (DGND), U9.6 (GND), U10.1 (GND)
unnamed: C1.2, R2.2, R9.1, U2.2 (-)
unnamed: C22.2, R3.1, R4.2, R10.1, U1.6 (-)
unnamed: C23.1, R8.1, R9.2
unnamed: C24.1, U5.71 (VCAP1)
unnamed: C25.1, U5.106 (VCAP2)
unnamed: C26.2, R11.2, R15.1, U2.6 (-)
unnamed: C27.2, R12.1, R13.2, R18.1, U1.2 (-)
unnamed: C28.2, R16.1, R17.2, R19.1, U3.13 (-)
unnamed: C29.1, U5.23 (PH0), Y1.2
unnamed: C30.1, R14.1, R15.2
unnamed: C31.1, U5.24 (PH1), Y1.1
unnamed: C32.1, R20.1, R28.2, U2.8
unnamed: C33.2, R21.1, R22.2, R26.1, U1.9 (-)
unnamed: C34.2, R23.1, R24.2, R27.1, U3.2 (-)
unnamed: C35.1, R30.1, R34.2, U2.14
unnamed: C36.2, R32.1, R33.2, R35.1, U1.13 (-)
unnamed: C42.1, U8.2 (CAPP)
unnamed: C42.2, U8.4 (CAPM)
unnamed: C44.2, U8.18 (LDOO)
unnamed: C45.2, U9.1 (CB)
unnamed: C48.1, U8.5 (VNEG)
unnamed: C49.1, R41.1
unnamed: C50.1, R42.1
unnamed: C51.1, R43.1
unnamed: C52.1, R44.1
unnamed: C56.1, R45.1
unnamed: R1.1, R5.1, R6.2, R7.1, U3.6 (-)
unnamed: R25.1, R29.2, U6.1
unnamed: R25.2, R28.1, U6.2 (-)
unnamed: R31.1, R36.2, U6.7
unnamed: R31.2, R34.1, U6.6 (-)
unnamed: R37.1, R43.2, U7.2 (I_IN1)
unnamed: R38.1, R44.2, U7.7 (I_IN2)
unnamed: R39.1, R41.2, U7.10 (I_IN3)
unnamed: R40.1, R42.2, U7.15 (I_IN4)
unnamed: R45.2, U7.1 (MODE)
VCC: C43.1, C53.2, C54.1, C59.1, C60.1, D1.1 (K), TP5.1, U2.4 (V+), U6.8 (V+), U7.16 (V+), U9.7 (VIN)
VEE: C57.2, D3.2 (A), R46.1, TP6.1, U2.11 (V-), U6.4 (V-), U7.9 (V-)

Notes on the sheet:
Input Scaling
Output Amplifiers and Buffers
DAC and VCA
POT Full scale: 3.3V CV Full scale: 6.4V
FLT: connect to ground for higher latency but less ringing
Full Scale: 7V
Power
C54: 47uF 25V MLCC on Prototype
DRAM
Headers and Connectors
Output Mixers and Inverting Buffers
Wet Output Amplifiers
Microcontroller
Tantalum
Test Points
AS3364D (linear VCA) with R43 and C56 in place; Remove for SSI2164 (exponential)

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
